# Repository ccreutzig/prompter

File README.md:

# prompter (with lights)

Project goal: For a puppetteer's stage, control both a text display on an Android tablet and LED lighting for the stage.

More details to follow.

Project stage: collecting requirements

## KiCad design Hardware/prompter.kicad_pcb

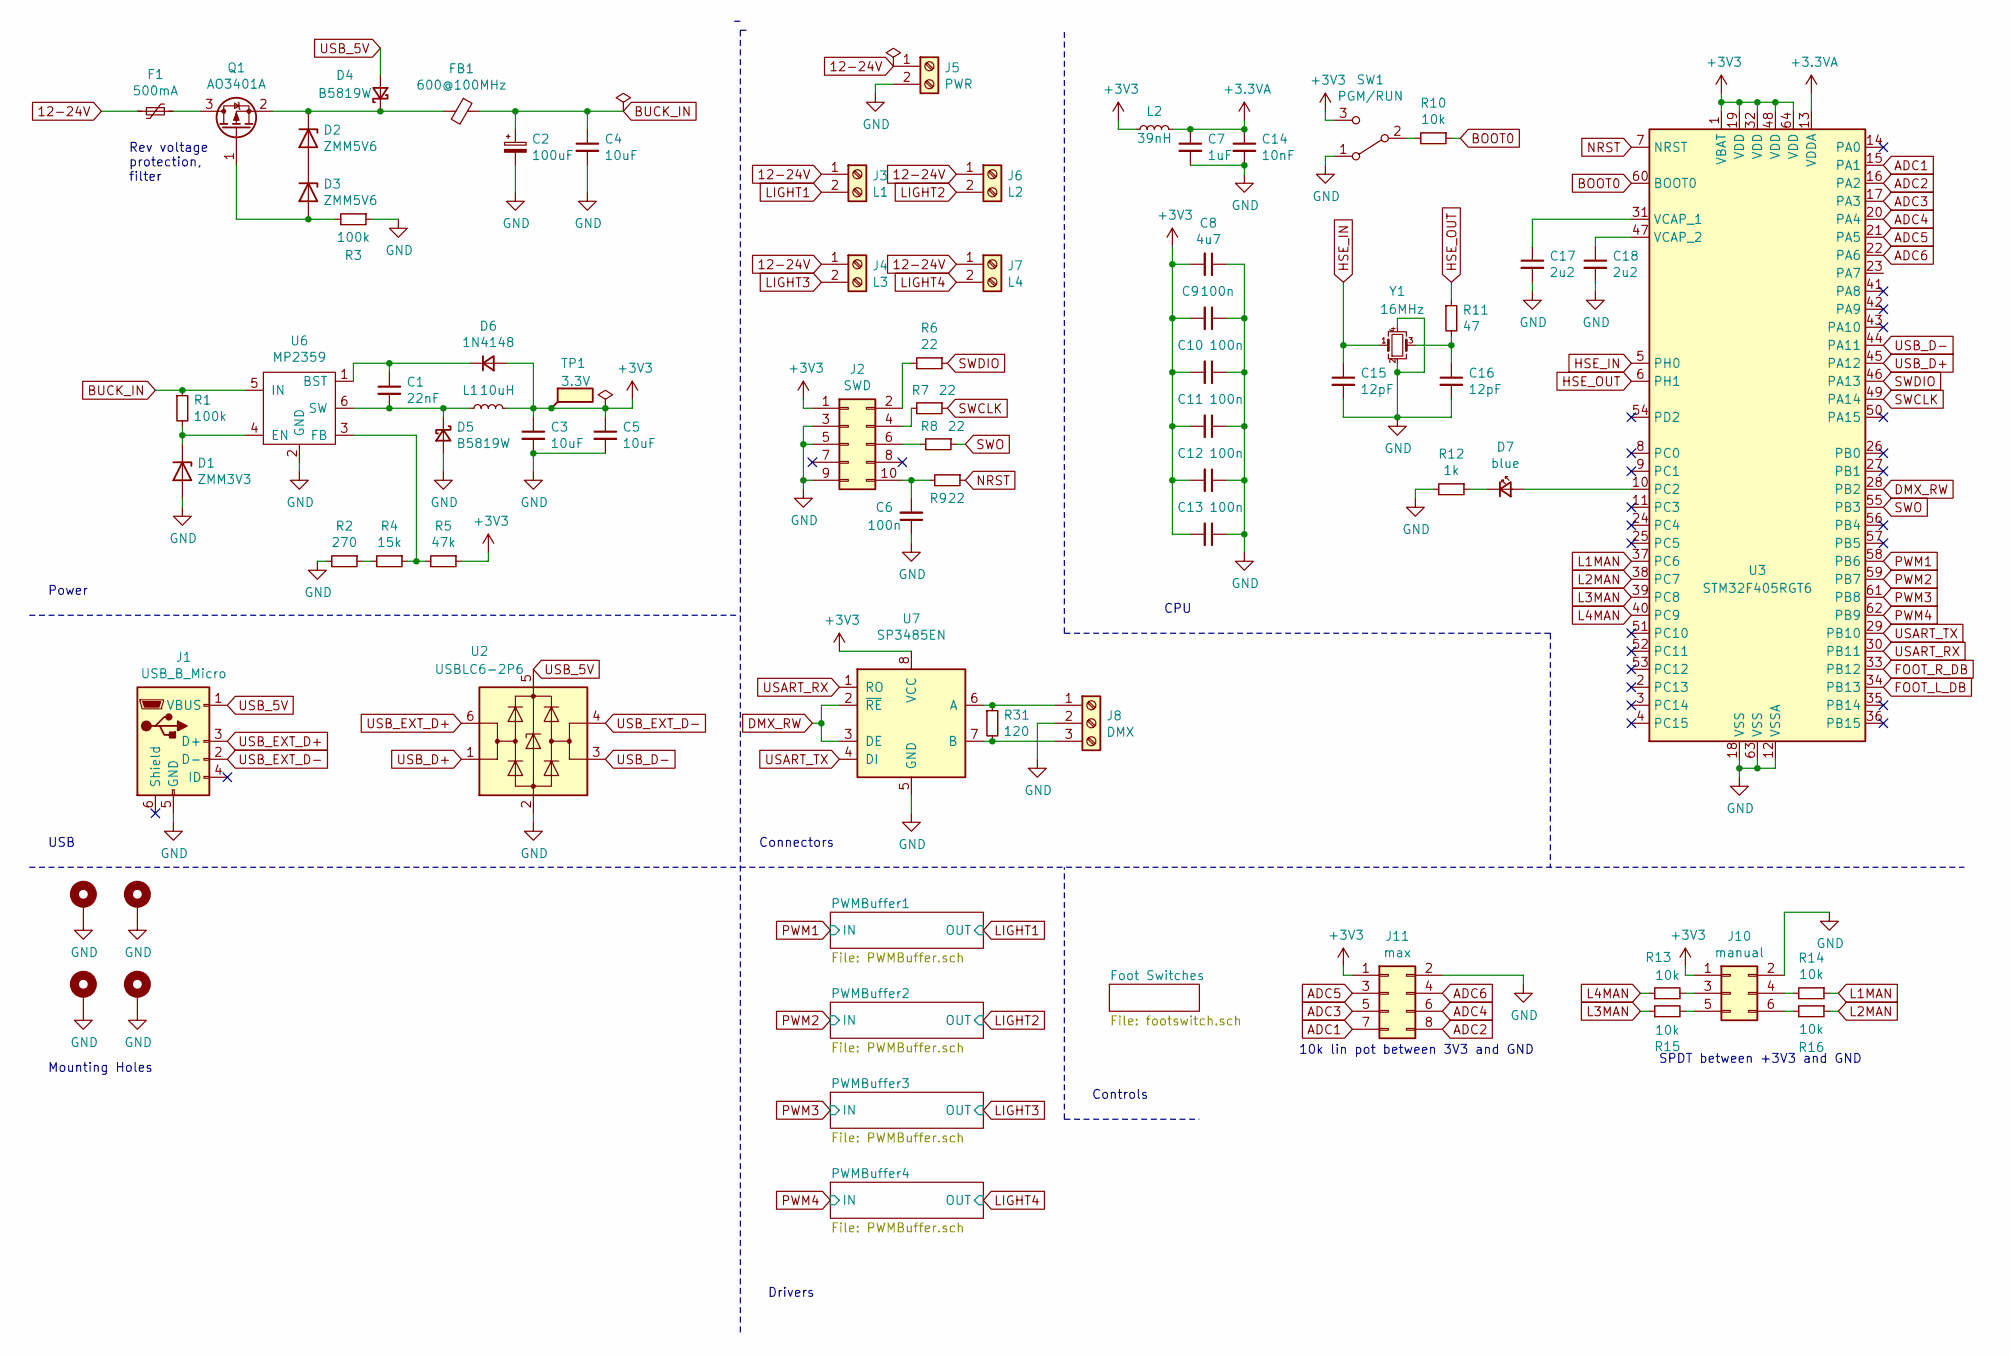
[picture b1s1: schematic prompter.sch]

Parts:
C1: 22nF; C_0805; LCSC C1729
C2: 100uF; CP_Tantalum_Case-B_EIA-3528-21_Reflow; LCSC C16133
C3, C4, C5: 10uF; C_1206; LCSC C13585
C6: 100n; C_0402
C7: 1uF; C_0402; LCSC C52923
C8: 4u7; C_0603; LCSC C19666
C9, C10, C11, C12, C13: 100n; C_0402; LCSC C1525
C14: 10nF; C_0402; LCSC C15195
C15, C16: 12pF; C_0402; LCSC C1547
C17, C18: 2u2; C_0603; LCSC C23630
D1: ZMM3V3; D_MiniMELF; LCSC C8056
D2, D3: ZMM5V6; D_MiniMELF; LCSC C8062
D4, D5: B5819W; D_SOD-123; LCSC C8598
D6: 1N4148; D_SOD-123; LCSC C81598
D7: blue; LED_0603; LCSC C72041
F1: 500mA; R_1812_HandSoldering
FB1: 600@100MHz; R_0805_HandSoldering; LCSC C1017
H1, H2, H3, H4: MountingHole_Pad; MountingHole_4.3x6.2mm_M4_Pad_Via
J1: USB_B_Micro; USB_Micro-B
J2: SWD; Pin_Header_Straight_2x05_Pitch2.54mm
J3: L1; PhoenixContact_MCV-G_02x3.50mm_Vertical
J4: L3; PhoenixContact_MCV-G_02x3.50mm_Vertical
J5: PWR; PhoenixContact_MCV-G_02x3.50mm_Vertical
J6: L2; PhoenixContact_MCV-G_02x3.50mm_Vertical
J7: L4; PhoenixContact_MCV-G_02x3.50mm_Vertical
J8: DMX; PhoenixContact_MCV-G_03x3.50mm_Vertical
J10: manual; Pin_Header_Straight_2x03_Pitch2.54mm
J11: max; Pin_Header_Straight_2x04_Pitch2.54mm
L1: 10uH; Neosid_Inductor_Ms50
L2: 39nH; R_0402; LCSC C86063
Q1: AO3401A; SOT-23; LCSC C15127
R1, R3: 100k; R_0603; LCSC C25803
R2: 270; R_0603; LCSC C22966
R4: 15k; R_0603; LCSC C22809
R5: 47k; R_0603; LCSC C25819
R6, R7, R8, R9: 22; R_0402; LCSC C25092
R10, R13, R14, R15, R16: 10k; R_0402; LCSC C25744
R11: 47; R_0402; LCSC C25118
R12: 1k; R_0603; LCSC C21190
R31: 120; R_0402; LCSC C25079
SW1: PGM/RUN; Pin_Header_Straight_1x03_Pitch2.54mm
TP1: 3.3V; Measurement_Point_Round-SMD-Pad_Small
U2: USBLC6-2P6; SOT-666; LCSC C15999
U3: STM32F405RGT6; LQFP-64-1EP_10x10mm_Pitch0.5mm; LCSC C15742
U6: MP2359; TSOT-23-6; LCSC C14259
U7: SP3485EN; SOIC-8_3.9x4.9mm_Pitch1.27mm; LCSC C8963
Y1: 16MHz; Crystal_SMD_3225-4pin_3.2x2.5mm; LCSC C13738

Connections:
12-24V: F1.2, J3.1, J4.1, J5.1, J6.1, J7.1; also elsewhere on the board
+3.3VA: C7.1, C14.1, L2.2, U3.13 (VDDA)
+3V3: C3.1, C5.1, C8.2, C9.2, C10.2, C11.2, C12.2, C13.2, D6.2 (A), J2.1, J10.1, J11.1, L1.2, L2.1, R5.1, SW1.3 (C), TP1.1, U3.1 (VBAT), U3.19 (VDD), U3.32 (VDD), U3.48 (VDD), U3.64 (VDD), U7.8 (VCC); also elsewhere on the board
ADC1: J11.7, U3.15 (PA1)
ADC2: J11.8, U3.16 (PA2)
ADC3: J11.5, U3.17 (PA3)
ADC4: J11.6, U3.20 (PA4)
ADC5: J11.3, U3.21 (PA5)
ADC6: J11.4, U3.22 (PA6)
BOOT0: R10.1, U3.60 (BOOT0)
BUCK_IN: C2.1, C4.1, FB1.1, R1.1, U6.5 (IN)
DMX_RW: U3.28 (PB2), U7.2 (~RE~), U7.3 (DE)
FOOT_L_DB: U3.34 (PB13); also elsewhere on the board
FOOT_R_DB: U3.33 (PB12); also elsewhere on the board
GND: C2.2, C3.2, C4.2, C5.2, C6.1, C7.2, C8.1, C9.1, C10.1, C11.1, C12.1, C13.1, C14.2, C15.2, C16.2, C17.2, C18.2, D1.2 (A), D5.2 (A), H1.1, H2.1, H3.1, H4.1, J1.5 (GND), J2.3, J2.5, J2.9, J5.2, J8.2, J10.2, J11.2, R2.2, R3.1, R12.2, SW1.1 (A), U2.2 (GND), U3.12 (VSSA), U3.18 (VSS), U3.63 (VSS), U6.2 (GND), U7.5 (GND), Y1.2, Y1.4; also elsewhere on the board
HSE_IN: C15.1, U3.5 (PH0), Y1.1
HSE_OUT: R11.1, U3.6 (PH1)
L1MAN: R14.1, U3.37 (PC6)
L2MAN: R16.1, U3.38 (PC7)
L3MAN: R15.1, U3.39 (PC8)
L4MAN: R13.1, U3.40 (PC9)
LIGHT1: J3.2; also elsewhere on the board
LIGHT2: J6.2; also elsewhere on the board
LIGHT3: J4.2; also elsewhere on the board
LIGHT4: J7.2; also elsewhere on the board
NRST: R9.1, U3.7 (NRST)
unnamed: C1.1, D6.1 (K), U6.1 (BST)
unnamed: C1.2, D5.1 (K), L1.1, U6.6 (SW)
unnamed: C6.2, J2.10, R9.2
unnamed: C16.1, R11.2, Y1.3
unnamed: C17.1, U3.31 (VCAP_1)
unnamed: C18.1, U3.47 (VCAP_2)
unnamed: D1.1 (K), R1.2, U6.4 (EN)
unnamed: D2.1 (K), D4.1 (K), FB1.2, Q1.2 (S)
unnamed: D2.2 (A), D3.1 (K)
unnamed: D3.2 (A), Q1.1 (G), R3.2
unnamed: D7.1 (K), R12.1
unnamed: D7.2 (A), U3.10 (PC2)
unnamed: F1.1, Q1.3 (D)
unnamed: J2.2, R6.2
unnamed: J2.4, R7.2
unnamed: J2.6, R8.2
unnamed: J8.1, R31.1, U7.6 (A)
unnamed: J8.3, R31.2, U7.7 (B)
unnamed: J10.3, R13.2
unnamed: J10.4, R14.2
unnamed: J10.5, R15.2
unnamed: J10.6, R16.2
unnamed: R2.1, R4.2
unnamed: R4.1, R5.2, U6.3 (FB)
unnamed: R10.2, SW1.2 (B)
PWM1: U3.58 (PB6); also elsewhere on the board
PWM2: U3.59 (PB7); also elsewhere on the board
PWM3: U3.61 (PB8); also elsewhere on the board
PWM4: U3.62 (PB9); also elsewhere on the board
SWCLK: R7.1, U3.49 (PA14)
SWDIO: R6.1, U3.46 (PA13)
SWO: R8.1, U3.55 (PB3)
USART_RX: U3.30 (PB11), U7.1 (RO)
USART_TX: U3.29 (PB10), U7.4 (DI)
USB_5V: D4.2 (A), J1.1 (VBUS), U2.5 (VBUS)
USB_D+: U2.1 (I/O1), U3.45 (PA12)
USB_D-: U2.3 (I/O2), U3.44 (PA11)
USB_EXT_D+: J1.3 (D+), U2.6 (I/O1)
USB_EXT_D-: J1.2 (D-), U2.4 (I/O2)

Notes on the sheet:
Rev voltage protection, filter
Power
CPU
USB
Connectors
Controls
Drivers
Mounting Holes
10k lin pot between 3V3 and GND
SPDT between +3V3 and GND

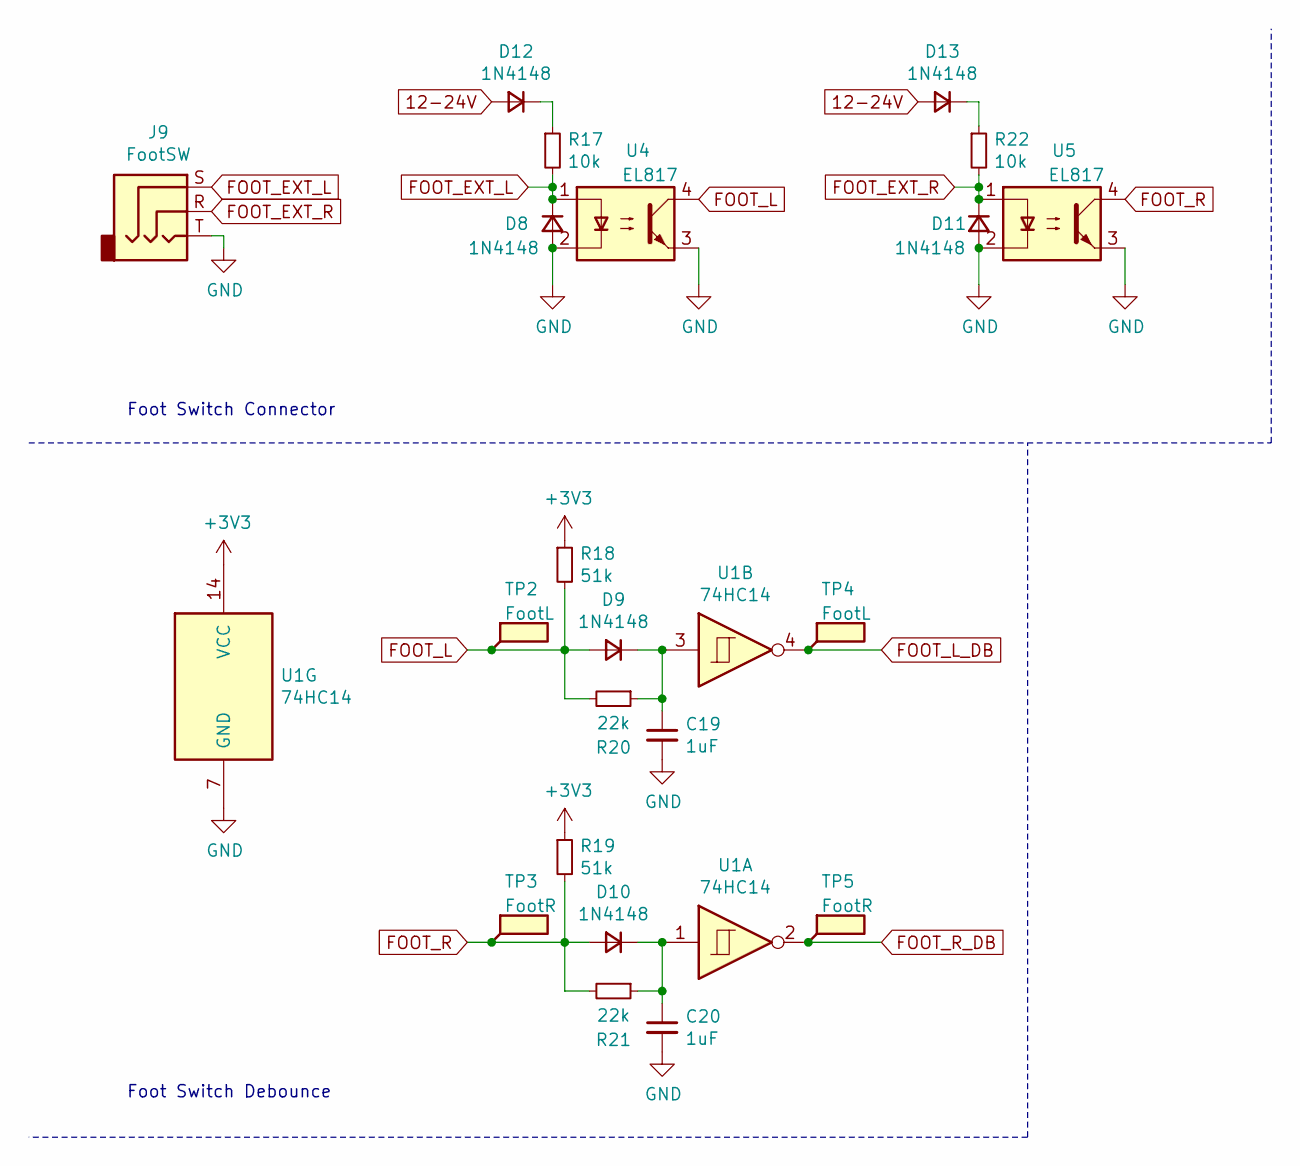
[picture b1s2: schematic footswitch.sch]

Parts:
C19, C20: 1uF; C_0402; LCSC C52923
D8, D9, D10, D11, D12, D13: 1N4148; D_SOD-123; LCSC C81598
J9: FootSW; Audio_Jack_6.35mm
R17, R22: 10k; R_0603; LCSC C25804
R18, R19: 51k; R_0402; LCSC C25794
R20, R21: 22k; R_0402; LCSC C25768
TP2, TP4: FootL; Measurement_Point_Round-SMD-Pad_Small
TP3, TP5: FootR; Measurement_Point_Round-SMD-Pad_Small
U1: 74HC14; SOIC-14_3.9x8.7mm_Pitch1.27mm; LCSC C5605
U4, U5: EL817; SO-4_7.6x3.6mm_Pitch2.54mm; LCSC C106900

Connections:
12-24V: D12.2 (A), D13.2 (A); also elsewhere on the board
+3V3: R18.1, R19.1, U1.14 (VCC); also elsewhere on the board
FOOT_EXT_L: D8.1 (K), J9.S, R17.2, U4.1
FOOT_EXT_R: D11.1 (K), J9.R, R22.2, U5.1
FOOT_L: D9.2 (A), R18.2, R20.2, TP2.1, U4.4
FOOT_L_DB: TP4.1, U1.4; also elsewhere on the board
FOOT_R: D10.2 (A), R19.2, R21.2, TP3.1, U5.4
FOOT_R_DB: TP5.1, U1.2; also elsewhere on the board
GND: C19.2, C20.2, D8.2 (A), D11.2 (A), J9.T, U1.7 (GND), U4.2, U4.3, U5.2, U5.3; also elsewhere on the board
unnamed: C19.1, D9.1 (K), R20.1, U1.3
unnamed: C20.1, D10.1 (K), R21.1, U1.1
unnamed: D12.1 (K), R17.1
unnamed: D13.1 (K), R22.1

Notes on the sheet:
Foot Switch Debounce
Foot Switch Connector

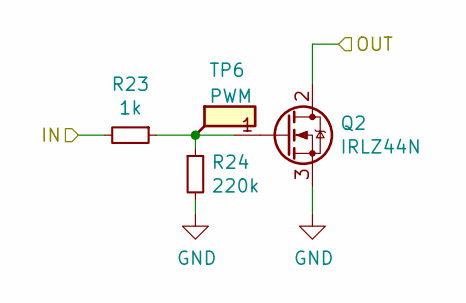
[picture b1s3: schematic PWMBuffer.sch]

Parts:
Q2: IRLZ44N; TO-220-3_Vertical
R23: 1k; R_0402; LCSC C11702
R24: 220k; R_0402; LCSC C25767
TP6: PWM; Measurement_Point_Round-SMD-Pad_Small

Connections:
GND: Q2.3 (S), R24.2; also elsewhere on the board
LIGHT1: Q2.2 (D); also elsewhere on the board
unnamed: Q2.1 (G), R23.1, R24.1, TP6.1
PWM1: R23.2; also elsewhere on the board

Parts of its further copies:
Q3, Q4, Q5: IRLZ44N; TO-220-3_Vertical
R25, R27, R29: 1k; R_0402; LCSC C11702
R26, R28, R30: 220k; R_0402; LCSC C25767
TP7, TP8, TP9: PWM; Measurement_Point_Round-SMD-Pad_Small

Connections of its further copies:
GND: Q3.3 (S), Q4.3 (S), Q5.3 (S), R26.2, R28.2, R30.2; also elsewhere on the board
LIGHT2: Q3.2 (D); also elsewhere on the board
LIGHT3: Q4.2 (D); also elsewhere on the board
LIGHT4: Q5.2 (D); also elsewhere on the board
unnamed: Q3.1 (G), R25.1, R26.1, TP7.1
unnamed: Q4.1 (G), R27.1, R28.1, TP8.1
unnamed: Q5.1 (G), R29.1, R30.1, TP9.1
PWM2: R25.2; also elsewhere on the board
PWM3: R27.2; also elsewhere on the board
PWM4: R29.2; also elsewhere on the board

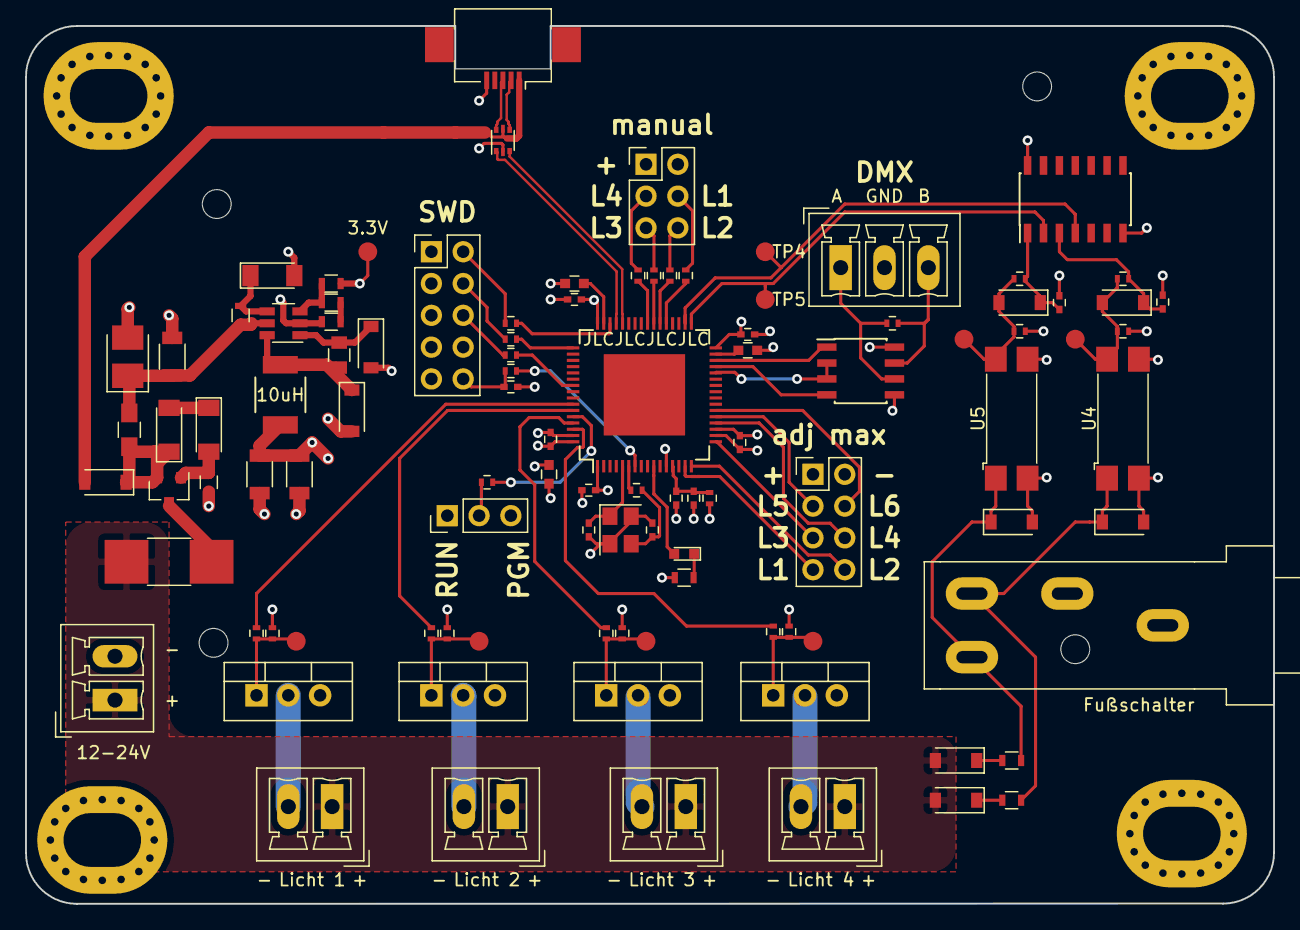
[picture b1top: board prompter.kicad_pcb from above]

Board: 4 copper layers, 99.7 x 70.1 mm, 106 parts (0 on the bottom side), 77 nets.

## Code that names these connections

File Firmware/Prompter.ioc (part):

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Mcu.Name=STM32F405RGTx
Mcu.Package=LQFP64
Mcu.UserName=STM32F405RGTx
PA1.Signal=ADCx_IN1
PA11.Mode=Device_Only
PA11.Signal=USB_OTG_FS_DM
PA12.Mode=Device_Only
PA12.Signal=USB_OTG_FS_DP
PA13.Mode=Trace_Asynchronous_SW
PA13.Signal=SYS_JTMS-SWDIO
PA14.Mode=Trace_Asynchronous_SW
PA14.Signal=SYS_JTCK-SWCLK
PA2.Signal=ADCx_IN2
PA3.Signal=ADCx_IN3
PA4.Signal=ADCx_IN4
PA5.Signal=ADCx_IN5
PA6.Signal=ADCx_IN6
PB10.Mode=Asynchronous
PB10.Signal=USART3_TX
PB11.Mode=Asynchronous
PB11.Signal=USART3_RX
PB12.GPIOParameters=GPIO_Label,GPIO_ModeDefaultEXTI
PB12.GPIO_Label=Foot L
PB12.GPIO_ModeDefaultEXTI=GPIO_MODE_IT_FALLING
PB12.Signal=GPXTI12
PB13.GPIOParameters=GPIO_Label,GPIO_ModeDefaultEXTI
PB13.GPIO_Label=Foot R
PB13.GPIO_ModeDefaultEXTI=GPIO_MODE_IT_FALLING
PB13.Signal=GPXTI13
PB2.GPIOParameters=GPIO_Label
PB2.GPIO_Label=DMX R/W
PB2.Signal=GPIO_Output
PB3.Mode=Trace_Asynchronous_SW
PB3.Signal=SYS_JTDO-SWO
PB6.GPIOParameters=GPIO_Label
PB6.GPIO_Label=PWM1
PB6.Signal=S_TIM4_CH1
PB7.GPIOParameters=GPIO_Label
PB7.GPIO_Label=PWM2
PB7.Signal=S_TIM4_CH2
PB8.GPIOParameters=GPIO_Label
PB8.GPIO_Label=PWM3
PB8.Signal=S_TIM4_CH3
PB9.GPIOParameters=GPIO_Label
PB9.GPIO_Label=PWM4
PB9.Signal=S_TIM4_CH4
PC2.GPIOParameters=GPIO_Label
PC2.GPIO_Label=Status LED
PC2.Signal=GPIO_Output
PC6.GPIOParameters=GPIO_PuPd,GPIO_Label
PC6.GPIO_Label=L1MAN
PC6.GPIO_PuPd=GPIO_NOPULL
PC6.Signal=GPIO_Input
PC7.GPIOParameters=GPIO_PuPd,GPIO_Label
PC7.GPIO_Label=L2MAN
PC7.GPIO_PuPd=GPIO_NOPULL
PC7.Signal=GPIO_Input
PC8.GPIOParameters=GPIO_PuPd,GPIO_Label
PC8.GPIO_Label=L3MAN
PC8.GPIO_PuPd=GPIO_NOPULL
PC8.Signal=GPIO_Input
PC9.GPIOParameters=GPIO_PuPd,GPIO_Label
PC9.GPIO_Label=L4MAN
PC9.GPIO_PuPd=GPIO_NOPULL
PC9.Signal=GPIO_Input
PH0-OSC_IN.Mode=HSE-External-Oscillator
PH0-OSC_IN.Signal=RCC_OSC_IN
PH1-OSC_OUT.Mode=HSE-External-Oscillator
PH1-OSC_OUT.Signal=RCC_OSC_OUT
RCC.HSE_VALUE=16000000
RCC.SYSCLKFreq_VALUE=16000000
board=custom

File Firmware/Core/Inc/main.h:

/* USER CODE BEGIN Header */
/**
  ******************************************************************************
  * @file           : main.h
  * @brief          : Header for main.c file.
  *                   This file contains the common defines of the application.
  ******************************************************************************
  * @attention
  *
  * <h2><center>&copy; Copyright (c) 2020 STMicroelectronics.
  * All rights reserved.</center></h2>
  *
  * This software component is licensed by ST under BSD 3-Clause license,
  * the "License"; You may not use this file except in compliance with the
  * License. You may obtain a copy of the License at:
  *                        opensource.org/licenses/BSD-3-Clause
  *
  ******************************************************************************
  */
/* USER CODE END Header */

/* Define to prevent recursive inclusion -------------------------------------*/
#ifndef __MAIN_H
#define __MAIN_H

#ifdef __cplusplus
extern "C" {
#endif

/* Includes ------------------------------------------------------------------*/
#include "stm32f4xx_hal.h"

/* Private includes ----------------------------------------------------------*/
/* USER CODE BEGIN Includes */

/* USER CODE END Includes */

/* Exported types ------------------------------------------------------------*/
/* USER CODE BEGIN ET */

/* USER CODE END ET */

/* Exported constants --------------------------------------------------------*/
/* USER CODE BEGIN EC */

/* USER CODE END EC */

/* Exported macro ------------------------------------------------------------*/
/* USER CODE BEGIN EM */

/* USER CODE END EM */

void HAL_TIM_MspPostInit(TIM_HandleTypeDef *htim);

/* Exported functions prototypes ---------------------------------------------*/
void Error_Handler(void);

/* USER CODE BEGIN EFP */

/* USER CODE END EFP */

/* Private defines -----------------------------------------------------------*/
#define Status_LED_Pin GPIO_PIN_2
#define Status_LED_GPIO_Port GPIOC
#define DMX_R_W_Pin GPIO_PIN_2
#define DMX_R_W_GPIO_Port GPIOB
#define Foot_L_Pin GPIO_PIN_12
#define Foot_L_GPIO_Port GPIOB
#define Foot_L_EXTI_IRQn EXTI15_10_IRQn
#define Foot_R_Pin GPIO_PIN_13
#define Foot_R_GPIO_Port GPIOB
#define Foot_R_EXTI_IRQn EXTI15_10_IRQn
#define L1MAN_Pin GPIO_PIN_6
#define L1MAN_GPIO_Port GPIOC
#define L2MAN_Pin GPIO_PIN_7
#define L2MAN_GPIO_Port GPIOC
#define L3MAN_Pin GPIO_PIN_8
#define L3MAN_GPIO_Port GPIOC
#define L4MAN_Pin GPIO_PIN_9
#define L4MAN_GPIO_Port GPIOC
#define PWM1_Pin GPIO_PIN_6
#define PWM1_GPIO_Port GPIOB
#define PWM2_Pin GPIO_PIN_7
#define PWM2_GPIO_Port GPIOB
#define PWM3_Pin GPIO_PIN_8
#define PWM3_GPIO_Port GPIOB
#define PWM4_Pin GPIO_PIN_9
#define PWM4_GPIO_Port GPIOB
/* USER CODE BEGIN Private defines */

/* USER CODE END Private defines */

#ifdef __cplusplus
}
#endif

#endif /* __MAIN_H */

/************************ (C) COPYRIGHT STMicroelectronics *****END OF FILE****/

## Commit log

2020-10-24 First draft, WIP
2020-10-25 for future extension, also added DMX hardware
2020-11-07 Board updates:
    Fixed footprints (SMD vs. THT, no hanging pads in the air)
    Added mounting holes for production
    Moved F.Fab text to readable locations
2020-11-26 Hardware v0.1, Firmware runs ADC trigger by TIM3
2020-11-30 bare essentials USB communication
    host -> device: "Ln mmm\n" sets channel n to mmm%
    device -> host: "L" or "R" for foot switch contact
